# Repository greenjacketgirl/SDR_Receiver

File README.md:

# SDR Receiver Project

**Introduction** | This project was created in the scope of the the class ENGR 357 "Engineering Electronics II" conducted through online learning at Walla Walla University. We ([Jordyn Watkins](https://github.com/greenjacketgirl) and [Joshua Silver](https://github.com/JoshSilver8)) were tasked with designing, building, and testing a *software defined radio (SDR) receiver*. Our radio is designed to listen to frequencies ranging from 500kHz - 50MHz designed to be used in conjunction with [Quisk](https://github.com/greenjacketgirl/SDR_Receiver/wiki/9.-Software), a free open source SDR software. For more information on the theory, reasoning behind our design choices, and a more in depth look at the results and specs of this project, please refer to the [Wiki](https://github.com/greenjacketgirl/SDR_Receiver/wiki) tab.

**Navigation** | This repository consists of several folders. In this "code" tab, you will find 2 primary folders: Attenuator and Receiver. Within the attenuator file, you will find a folder containing the KiCad files, a folder containing the LTspice simulation files, and a third folder containing build and test notes with pictures and other documentation. The Receiver folder contains 4 main folders: KiCad, LTSpice, Quisk, and Documentation.

**Results** | The radio is in working condition - producing low noise I and Q signals 90 degrees out of phase. The signal discernability is very good, being able to detect signals as small as 0.5uV, and the image rejection is also decent having a 30dB difference between signal and image. For more details on the specs for the radio, visit the [Results](https://github.com/greenjacketgirl/SDR_Receiver/wiki/Results) in the [Wiki](https://github.com/greenjacketgirl/SDR_Receiver/wiki).

**Credits** | This project was created with a lot of help from our professor, Dr. Frohne. The files under the Quisk folder are primarily his. See his github profile at https://github.com/frohro/ 

**Status of Project** | Visit the "issues" tab to see errors and fixes for this project - which should provide a more in depth explanation for the quote "status" of the project. You can also visit the "Wiki" page or view the documentation files in the folders for a description of build and test process when troubleshooting issues.

REVISION 1: _05/26/2020  Build Phase and Troubleshooting Hardware_ |
REVISION 2: _06/04/2020 Test Phase and Troubleshooting Quisk Software Integration_ | REVISION 3: _06/10/2020 Working Radio Fine Tuning and Adjustments_

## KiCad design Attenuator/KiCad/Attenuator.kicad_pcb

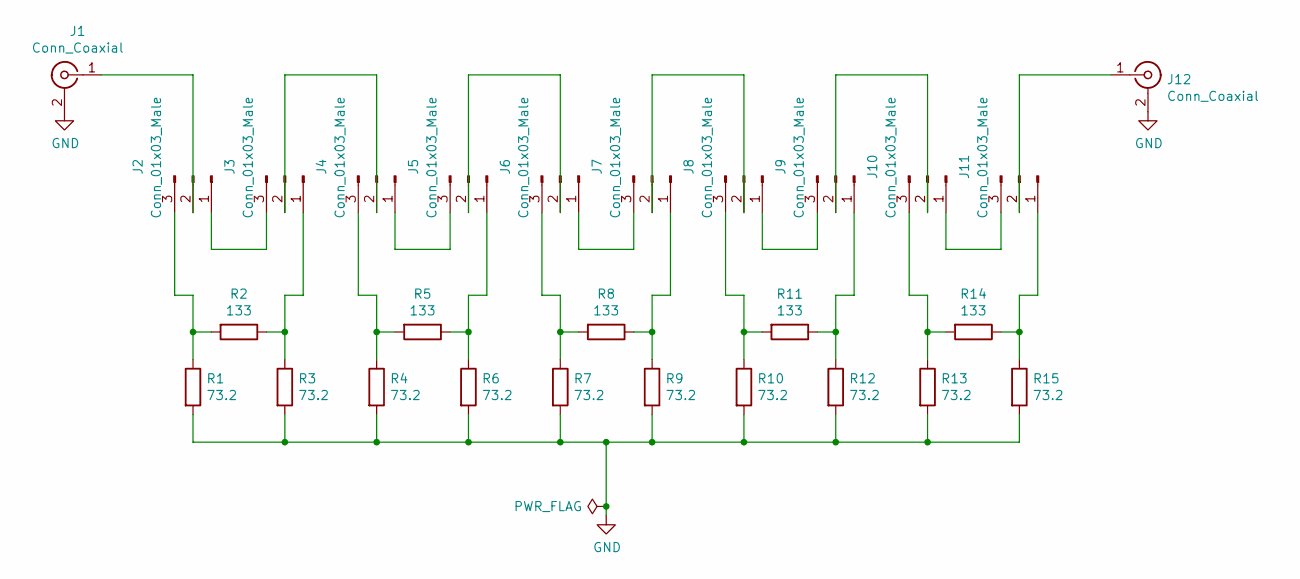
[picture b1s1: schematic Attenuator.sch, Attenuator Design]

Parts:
J1, J12: Conn_Coaxial; SMA_Molex_73251-1153_EdgeMount_Horizontal
J2, J3, J4, J5, J6, J7, J8, J9, J10, J11: Conn_01x03_Male; PinHeader_1x03_P2.54mm_Vertical
R1, R3, R4, R6, R7, R9, R10, R12, R13, R15: 73.2; R_Axial_DIN0207_L6.3mm_D2.5mm_P7.62mm_Horizontal
R2, R5, R8, R11, R14: 133; R_Axial_DIN0207_L6.3mm_D2.5mm_P7.62mm_Horizontal

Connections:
GND: J1.2 (Ext), J12.2 (Ext), R1.2, R3.2, R4.2, R6.2, R7.2, R9.2, R10.2, R12.2, R13.2, R15.2
unnamed: J1.1 (In), J2.2
unnamed: J2.1, J3.3
unnamed: J2.3, R1.1, R2.2
unnamed: J3.1, R2.1, R3.1
unnamed: J3.2, J4.2
unnamed: J4.1, J5.3
unnamed: J4.3, R4.1, R5.2
unnamed: J5.1, R5.1, R6.1
unnamed: J5.2, J6.2
unnamed: J6.1, J7.3
unnamed: J6.3, R7.1, R8.2
unnamed: J7.1, R8.1, R9.1
unnamed: J7.2, J8.2
unnamed: J8.1, J9.3
unnamed: J8.3, R10.1, R11.2
unnamed: J9.1, R11.1, R12.1
unnamed: J10.1, J11.3
unnamed: J9.2, J10.2
unnamed: J10.3, R13.1, R14.2
unnamed: J11.1, R14.1, R15.1
unnamed: J11.2, J12.1 (In)

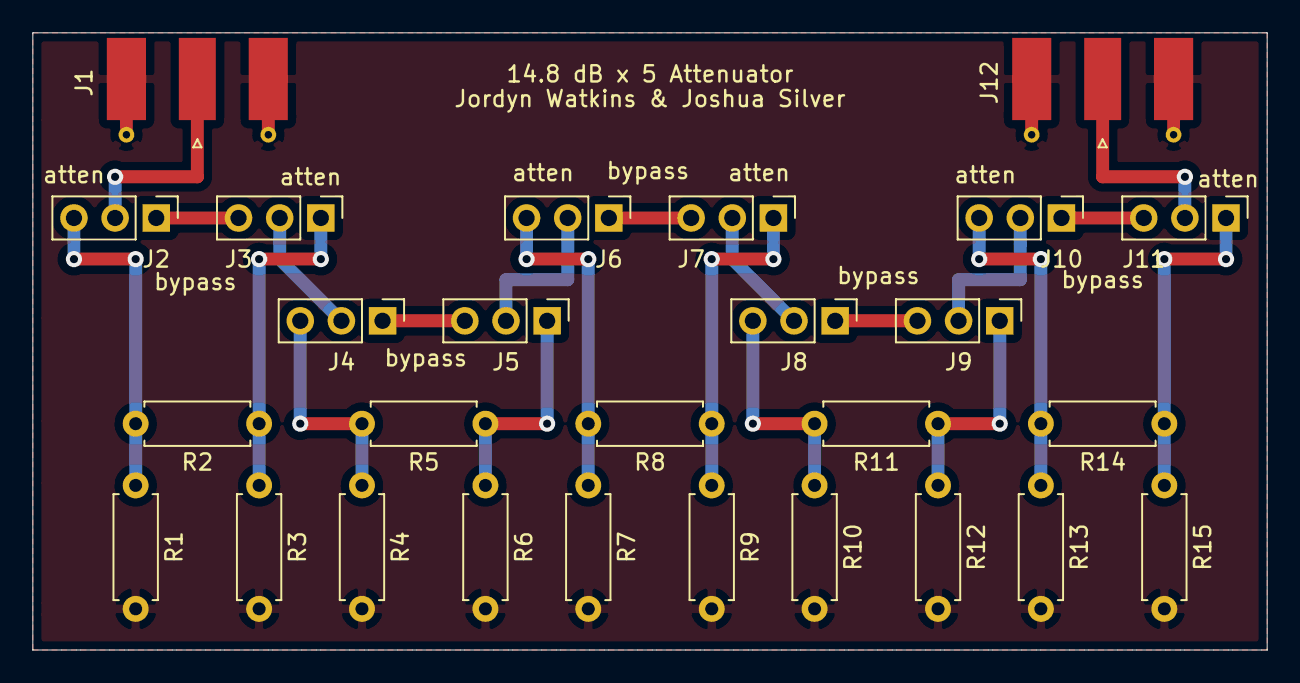
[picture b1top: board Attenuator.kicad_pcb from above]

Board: 2 copper layers, 76.2 x 38.1 mm, 27 parts (0 on the bottom side), 22 nets.

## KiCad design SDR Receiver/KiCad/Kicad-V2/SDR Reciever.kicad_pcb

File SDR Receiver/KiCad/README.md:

# Navigating this folder

This folder contains two versions of the schematic and pcb design. The first design is the collection of files shown. The second revision is located in the folder [Kicad-V2](https://github.com/greenjacketgirl/SDR_Receiver/tree/master/SDR%20Receiver/KiCad/Kicad-V2). This second revision is the schematic updated with the corrections made by hand shown in the [Issues tab](https://github.com/greenjacketgirl/SDR_Receiver/issues). Note that this second revision only has an updated schematic, not an updated pcb. Thus, future work will require further revision of the PCB. 

Primary corrections made in this second revision:
* crystal footprint pin numbers corrected
* pull up resistors on si5351 clock generator connected to VCC instead of GND
* bandpass filter wiring correction on multiplexer
* label correction from tayloe mixer to summing op-amps

I tried to include the .pretty and library files for the footprints and schematic symbols I used. If you have a difficult time seeing the footprints for some reason, you can also refer to our digikey BOM in the [documents section](https://github.com/greenjacketgirl/SDR_Receiver/tree/master/SDR%20Receiver/Documentation) to look up the part on the [digikey website](https://www.digikey.com) and download the respective footprint from there. You may need to also make corrections to the PCB board after uploading a new symbol and footprint .pretty file.

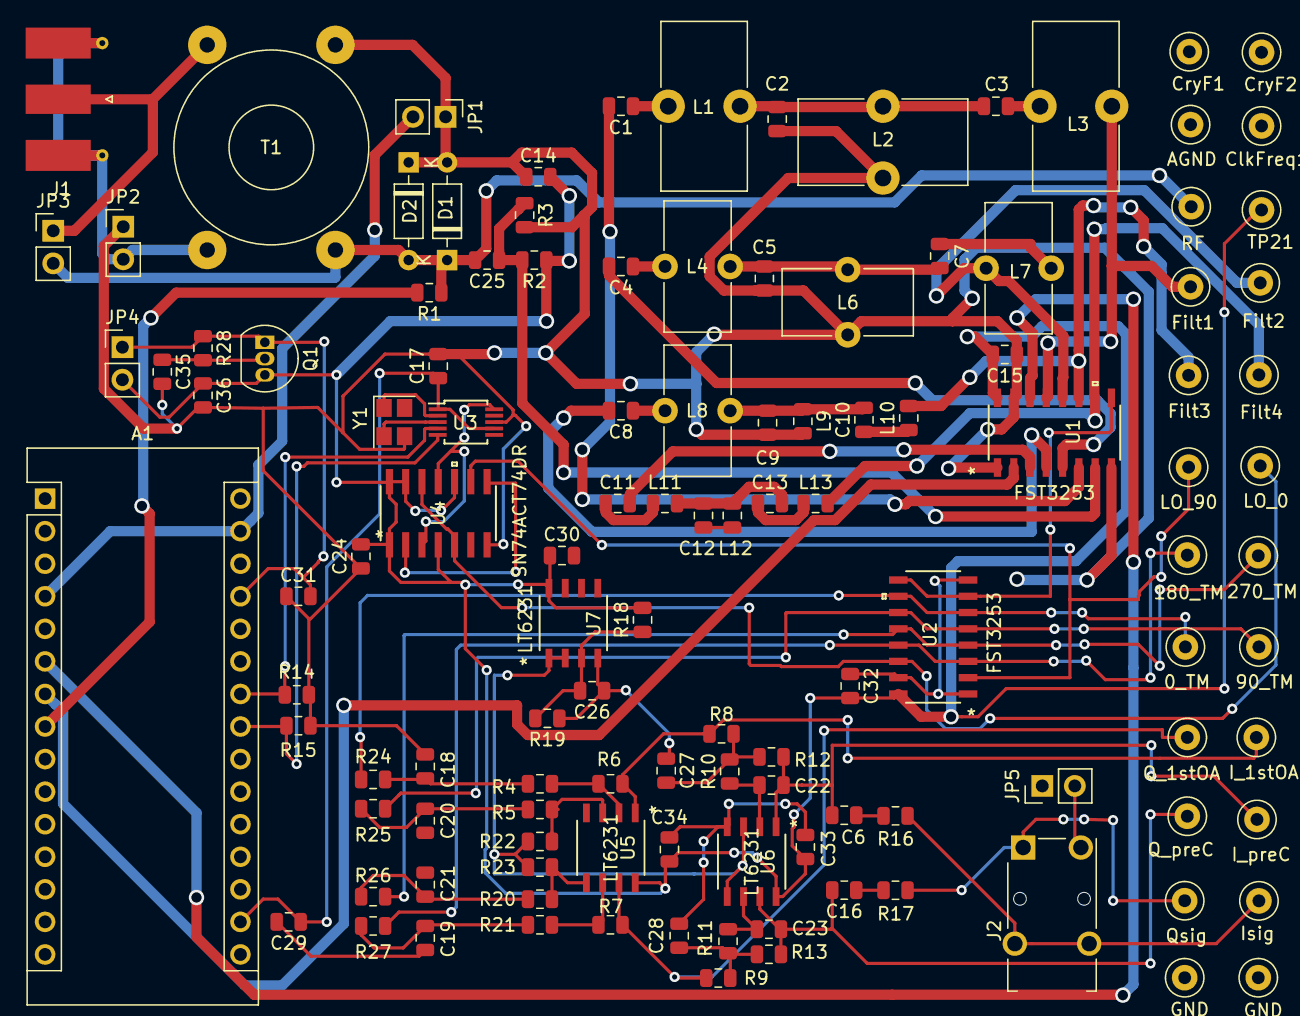
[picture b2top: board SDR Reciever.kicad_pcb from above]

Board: 2 copper layers, 120 parts (0 on the bottom side), 69 nets.

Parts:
A1: Arduino Nano V3; Arduino_Nano
C1, C3: 2.2nF; C_0805_2012Metric
C2: 3.3nF; C_0805_2012Metric
C4, C7: 680pF; C_0805_2012Metric
C5: 1.3nF; C_0805_2012Metric
C6, C16, C26, C35: 10uF; C_0805_2012Metric
C8, C10: 240pF; C_0805_2012Metric
C9: 510pF; C_0805_2012Metric
C11, C13: 91pF; C_0805_2012Metric
C12: 220pF; C_0805_2012Metric
C14, C25, C29, C30, C31, C32, C33, C34, C36: 0.1uF; C_0805_2012Metric
C15, C17, C24: 0.1u; C_0805_2012Metric
C18, C19, C20, C21: 17nF; C_0805_2012Metric
C22, C23: 1nF; C_0805_2012Metric
C27, C28: 22.6nF; C_0805_2012Metric
ClkFreq1: TP24; TestPoint_Loop_D1.80mm_Drill1.0mm_Beaded
CryF1: TP22; TestPoint_Loop_D1.80mm_Drill1.0mm_Beaded
CryF2: TP23; TestPoint_Loop_D1.80mm_Drill1.0mm_Beaded
D1, D2: D; D_DO-35_SOD27_P7.62mm_Horizontal
J1: Conn_Coaxial; SMA_Molex_73251-1153_EdgeMount_Horizontal
J2: AudioJack3; Jack_3.5mm_Switronic_ST-005-G_horizontal
JP1: Jumper_NC_Small; PinHeader_1x02_P2.54mm_Vertical
JP2, JP3, JP4, JP5: Jumper; PinHeader_1x02_P2.54mm_Vertical
L1, L3: 3.9uH; L_Toroid_Vertical_L13.0mm_W6.5mm_P5.60mm
L2: 2.7uH; L_Toroid_Vertical_L13.0mm_W6.5mm_P5.60mm
L4, L7: 1.6 uH; L_Toroid_Vertical_L10.0mm_W5.0mm_P5.08mm
L6: 820nH; L_Toroid_Vertical_L10.0mm_W5.0mm_P5.08mm
L8: 680nH; L_Toroid_Vertical_L10.0mm_W5.0mm_P5.08mm
L9: 300nH; L_0805_2012Metric
L10: 680nH; L_0805_2012Metric
L11, L13: 270nH; L_0805_2012Metric
L12: 120nH; L_0805_2012Metric
Q1: BC237; TO-92_Inline
R1: 2.2k; R_0805_2012Metric
R2, R3, R18, R19, R22, R23: 10k; R_0805_2012Metric
R4, R5, R20, R21: 50; R_0805_2012Metric
R6, R7: 10K; R_0805_2012Metric
R8, R9: 866; R_0805_2012Metric
R10, R11: 1.1k; R_0805_2012Metric
R12, R13: 8.66k; R_0805_2012Metric
R14, R15: 4.7k; R_0805_2012Metric
R16, R17: 100; R_0805_2012Metric
R24, R25, R26, R27: 46; R_0805_2012Metric
R28: 1k; R_0805_2012Metric
T1: Transformer_1P_1S; Transformer_Toroid_Horizontal_D14.0mm_Amidon-T50
TP1, TP2: GND; TestPoint_Loop_D1.80mm_Drill1.0mm_Beaded
TP3: RF; TestPoint_Loop_D1.80mm_Drill1.0mm_Beaded
TP4: Filt1; TestPoint_Loop_D1.80mm_Drill1.0mm_Beaded
TP5: Filt2; TestPoint_Loop_D1.80mm_Drill1.0mm_Beaded
TP6: Filt3; TestPoint_Loop_D1.80mm_Drill1.0mm_Beaded
TP7: Filt4; TestPoint_Loop_D1.80mm_Drill1.0mm_Beaded
TP8: LO_90; TestPoint_Loop_D1.80mm_Drill1.0mm_Beaded
TP9: LO_0; TestPoint_Loop_D1.80mm_Drill1.0mm_Beaded
TP10: I_1stOA; TestPoint_Loop_D1.80mm_Drill1.0mm_Beaded
TP11: Q_1stOA; TestPoint_Loop_D1.80mm_Drill1.0mm_Beaded
TP12: I_preC; TestPoint_Loop_D1.80mm_Drill1.0mm_Beaded
TP13: Q_preC; TestPoint_Loop_D1.80mm_Drill1.0mm_Beaded
TP14: 0_TM; TestPoint_Loop_D1.80mm_Drill1.0mm_Beaded
TP15: 90_TM; TestPoint_Loop_D1.80mm_Drill1.0mm_Beaded
TP16: 270_TM; TestPoint_Loop_D1.80mm_Drill1.0mm_Beaded
TP17: 180_TM; TestPoint_Loop_D1.80mm_Drill1.0mm_Beaded
TP18: Isig; TestPoint_Loop_D1.80mm_Drill1.0mm_Beaded
TP19: Qsig; TestPoint_Loop_D1.80mm_Drill1.0mm_Beaded
TP20: AGND; TestPoint_Loop_D1.80mm_Drill1.0mm_Beaded
TP21: 4.3V; TestPoint_Loop_D1.80mm_Drill1.0mm_Beaded
U1, U2: FST3253; FST3253MX
U3: Si5351A-B-GT; MSOP-10_3x3mm_P0.5mm
U4: SN74ACT74DR
U5, U6, U7: LT6231; LT6231CS8-PBF
Y1: CX3225; Crystal_SMD_SeikoEpson_FA238-4Pin_3.2x2.5mm

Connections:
3.3V: A1.17, C17.1, C29.1, R14.2, R15.2, U3.1, U3.7
4.3V: C14.2, C15.2, C24.2, C30.1, C32.2, C33.1, C34.1, C36.1, JP4.2, Q1.3, R2.1, R18.2, TP21.1, U1.16, U2.16, U4.1, U4.4, U4.10, U4.13, U4.14, U5.8, U6.8, U7.8
5V: A1.27, C31.2, JP4.1, Q1.1, R28.1
/I(t): J2.T, R16.1, TP18.1
/IF(0): C20.1, R4.2, R24.1
/IF(90): C21.1, R20.2, R25.1
/IF(180): C19.1, R5.2, R27.1
/IF(270): C18.1, R21.2, R26.1
/Q(t): J2.R, R17.1, TP19.1
/SCL: A1.24, R14.1, U3.4
/SDA: A1.23, R15.1, U3.5
AGND: R22.1, R23.2, TP20.1, U6.3, U6.5, U7.1, U7.2
CLKOUT: ClkFreq1.1, U3.10, U4.3, U4.11
D3: A1.6, U1.14
D4: A1.7, U1.2
GND: C2.1, C5.1, C9.1, C12.1, C14.1, C15.1, C17.2, C18.2, C19.2, C20.2, C21.2, C24.1, C26.1, C27.1, C28.2, C29.2, C30.2, C31.1, C32.1, C33.2, C34.2, C35.2, C36.2, D1.1, D2.2, JP1.1, JP2.1, JP5.1, L2.2, L6.2, L9.2, L12.2, R3.2, R19.1, T1.3, TP1.1, TP2.1, U1.1, U1.8, U1.15, U2.1, U2.8, U2.15, U3.8, U4.7, U5.4, U6.4, U7.4, Y1.2, Y1.4
LO(0): TP9.1, U2.14, U4.5, U4.12
LO(90): TP8.1, U2.2, U4.9
MUTE: A1.8, R1.1
unnamed: A1.4, A1.29, JP1.2
unnamed: C1.1, L1.1
unnamed: C1.2, U1.6
unnamed: C2.2, C3.1, L1.2, L2.1
unnamed: C3.2, L3.1
unnamed: C4.1, L4.1
unnamed: C4.2, U1.5
unnamed: C5.2, C7.2, L4.2, L6.1
unnamed: C6.1, R16.2
unnamed: C7.1, L7.1
unnamed: C8.1, L8.1
unnamed: C8.2, U1.4
unnamed: C10.1, L10.1
unnamed: C9.2, C10.2, L8.2, L9.1
unnamed: C11.1, L11.1
unnamed: C11.2, U1.3
unnamed: C12.2, C13.2, L11.2, L12.1
unnamed: C13.1, L13.1
unnamed: C16.1, R17.2
unnamed: C16.2, C23.1, R13.2, TP13.1, U6.7
unnamed: C6.2, C22.1, R12.2, TP12.1, U6.1
unnamed: C22.2, R10.1, U6.2
unnamed: C23.2, R11.1, U6.6
unnamed: C25.2, D1.2, D2.1, JP3.2, R1.2, T1.4, TP3.1
unnamed: C26.2, R18.1, R19.2, U7.3
unnamed: C27.2, R8.1, R10.2, R12.1
unnamed: C28.1, R9.1, R11.2, R13.1
unnamed: C35.1, Q1.2, R28.2
unnamed: CryF1.1, U3.2, Y1.1
unnamed: CryF2.1, U3.3, Y1.3
unnamed: J1.1, JP3.1, T1.1
unnamed: J1.2, JP2.2, T1.2
unnamed: J2.S, JP5.2
unnamed: L3.2, TP4.1, U1.10
unnamed: L7.2, TP5.1, U1.11
unnamed: L10.2, TP6.1, U1.12
unnamed: L13.2, TP7.1, U1.13
unnamed: R4.1, R6.2, U5.2
unnamed: R6.1, R8.2, TP10.1, U5.1
unnamed: R7.1, R9.2, TP11.1, U5.7
unnamed: R20.1, R23.1, U5.5
unnamed: R7.2, R21.1, U5.6
unnamed: R5.1, R22.2, U5.3
unnamed: R24.2, TP14.1, U2.6, U2.10
unnamed: R25.2, TP15.1, U2.5, U2.11
unnamed: R26.2, TP16.1, U2.4, U2.12
unnamed: R27.2, TP17.1, U2.3, U2.13
unnamed: U4.2, U4.8
RF: U1.9, U2.7, U2.9
signal: C25.1, R2.2, R3.1, U1.7

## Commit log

2020-05-27 Add files via upload
    Added Frohro 's Arduino test file
2020-05-27 Create README.md
    Adding Instructional README first revision
2020-05-27 Add files via upload
    Attenuator Files Uploaded -- files need to be revised to match corrections that need to be made in the project
2020-05-27 Add files via upload
    Receiver files uploaded --- files need to be revised and cleaned up to match corrections that need to be made on the project
2020-05-27 Add files via upload
    Quisk files and Arduino Code from Frohro github
2020-06-08 Adding Photos folder
2020-06-11 Added Cover Photo
2020-06-11 Rename AboutSimulation.md to README.md
2020-06-11 added pdf document of updated schematic

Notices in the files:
parts and their libraries:
Copyright 2016 Accelerated Designs. All rights reserved.
